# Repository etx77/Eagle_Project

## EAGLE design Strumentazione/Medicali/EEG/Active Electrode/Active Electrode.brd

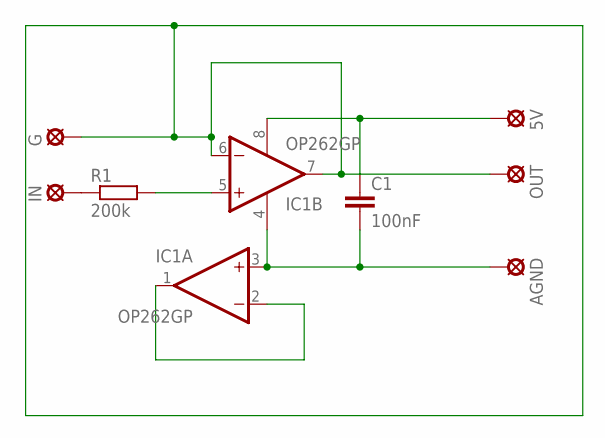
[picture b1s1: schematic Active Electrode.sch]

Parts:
5V: LSP10
AGND: LSP10
C1: 100nF; C025-024X044
G: LSP10
IC1: OP262GP; DIL08
IN: LSP10
OUT: LSP10
R1: 200k; 0204/5

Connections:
unnamed: IC1.1 (OUT), IC1.2 (-IN)
unnamed: AGND.MP, C1.2, IC1.3 (+IN), IC1.4 (V-)
unnamed: IC1.5 (+IN), R1.2
unnamed: IN.MP, R1.1
unnamed: 5V.MP, C1.1, IC1.8 (V+)
unnamed: G.MP, IC1.6 (-IN), IC1.7 (OUT), OUT.MP

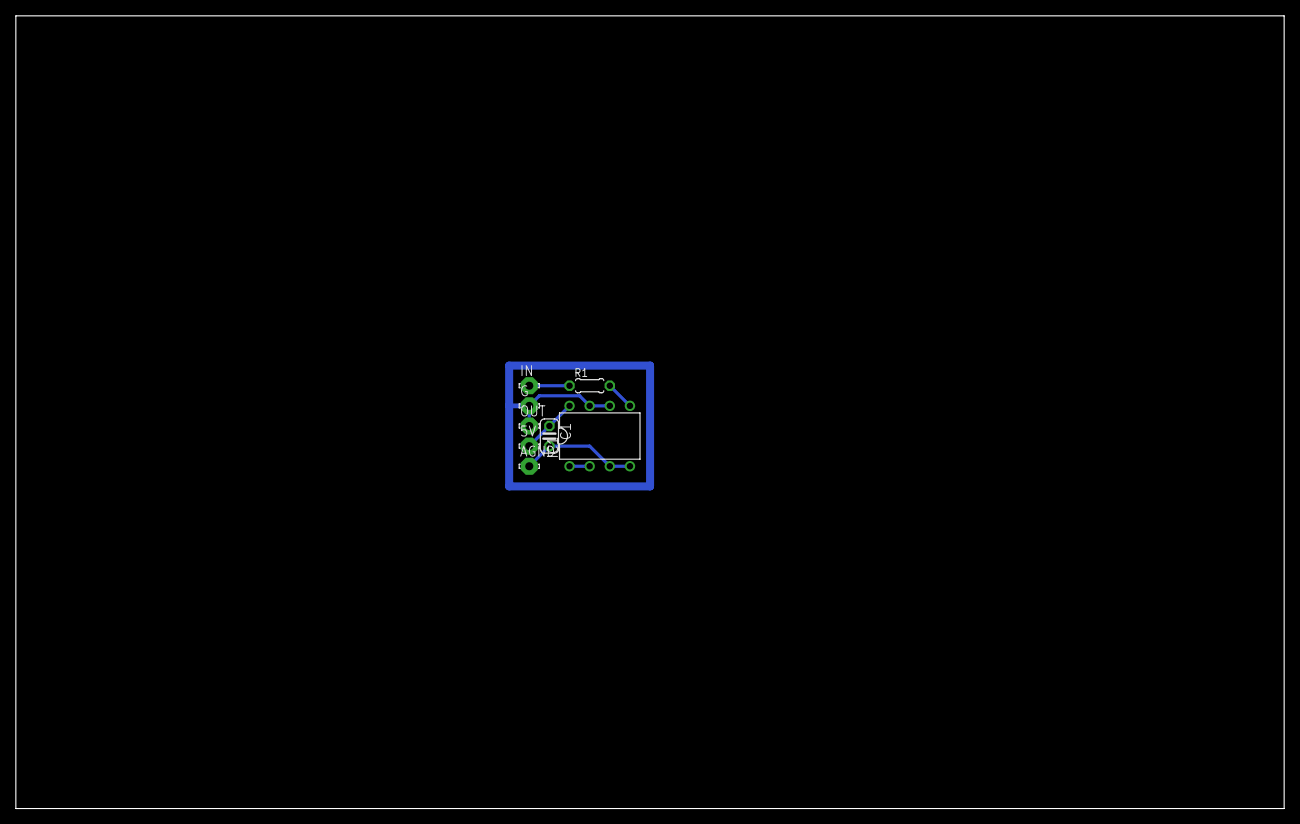
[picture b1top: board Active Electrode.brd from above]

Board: 2 copper layers, 160.0 x 100.0 mm, 8 parts (0 on the bottom side), 6 nets.

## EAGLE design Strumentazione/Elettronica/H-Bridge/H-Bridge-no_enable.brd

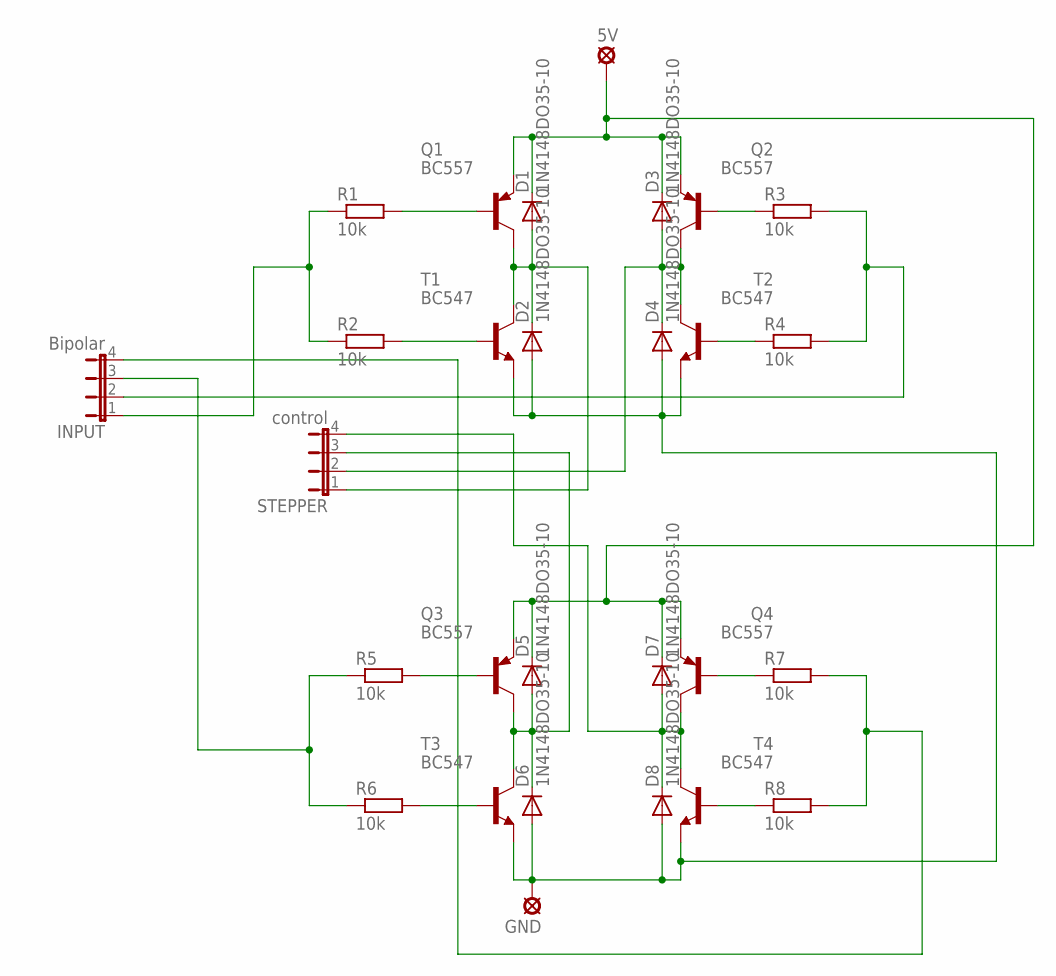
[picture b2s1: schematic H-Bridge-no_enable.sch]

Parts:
5V: LSP10
D1, D2, D3, D4, D5, D6, D7, D8: 1N4148DO35-10; DO35-10
GND: LSP10
INPUT: Bipolar; JP4
Q1, Q2, Q3, Q4: BC557; TO92
R1, R2, R3, R4, R5, R6, R7, R8: 10k; 0204V
STEPPER: control; JP4
T1, T2, T3, T4: BC547; TO92

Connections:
unnamed: INPUT.1, R1.1, R2.1
unnamed: Q1.2 (B), R1.2
unnamed: R2.2, T1.2 (B)
unnamed: D1.A, D2.C, Q1.3 (C), STEPPER.1, T1.3 (C)
unnamed: D3.A, D4.C, Q2.3 (C), STEPPER.2, T2.3 (C)
unnamed: Q2.2 (B), R3.1
unnamed: R4.1, T2.2 (B)
unnamed: INPUT.2, R3.2, R4.2
unnamed: D2.A, D4.A, D6.A, D8.A, GND.MP, T1.1 (E), T2.1 (E), T3.1 (E), T4.1 (E)
unnamed: INPUT.3, R5.1, R6.1
unnamed: Q3.2 (B), R5.2
unnamed: R6.2, T3.2 (B)
unnamed: D5.A, D6.C, Q3.3 (C), STEPPER.3, T3.3 (C)
unnamed: D7.A, D8.C, Q4.3 (C), STEPPER.4, T4.3 (C)
unnamed: Q4.2 (B), R7.1
unnamed: R8.1, T4.2 (B)
unnamed: INPUT.4, R7.2, R8.2
unnamed: 5V.MP, D1.C, D3.C, D5.C, D7.C, Q1.1 (E), Q2.1 (E), Q3.1 (E), Q4.1 (E)

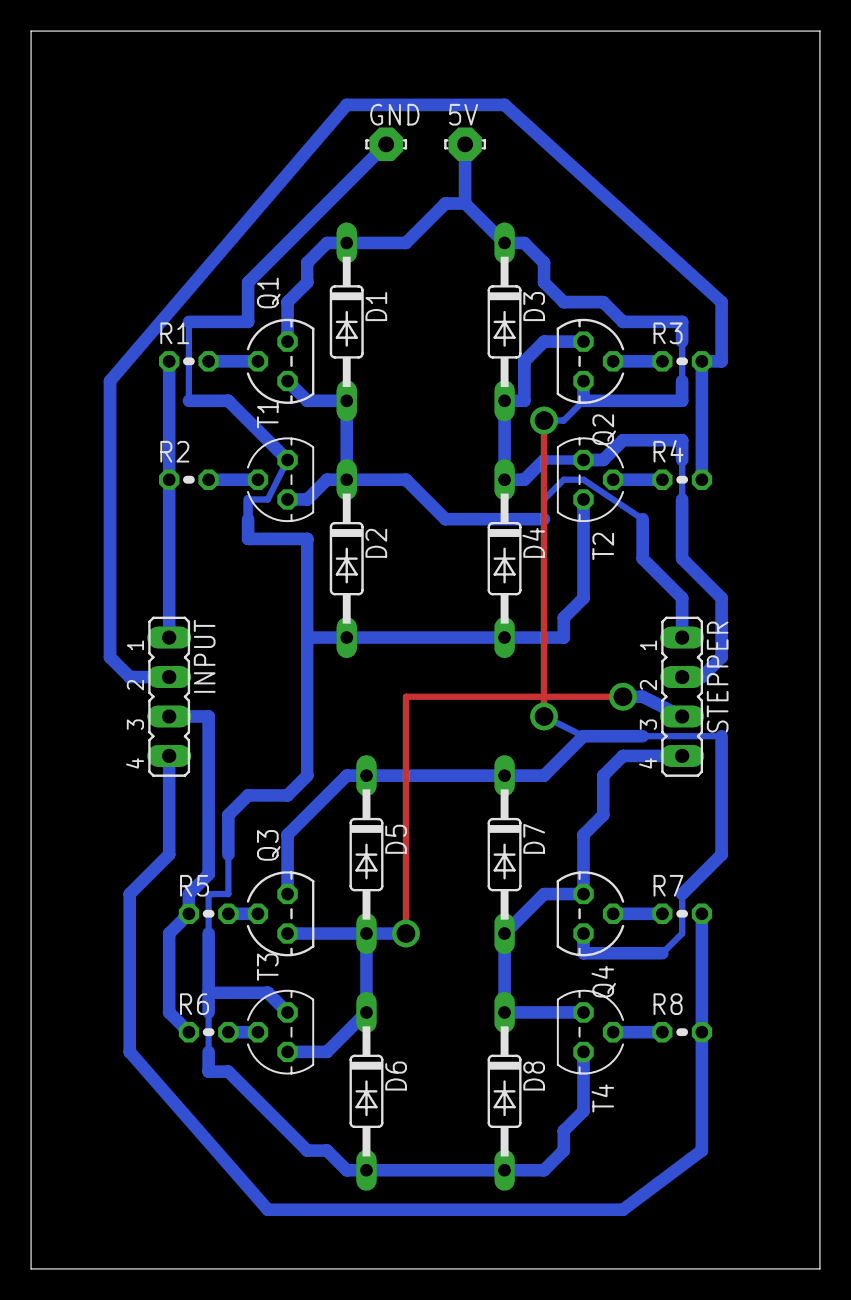
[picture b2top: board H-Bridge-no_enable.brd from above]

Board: 2 copper layers, 50.8 x 79.7 mm, 28 parts (0 on the bottom side), 18 nets.

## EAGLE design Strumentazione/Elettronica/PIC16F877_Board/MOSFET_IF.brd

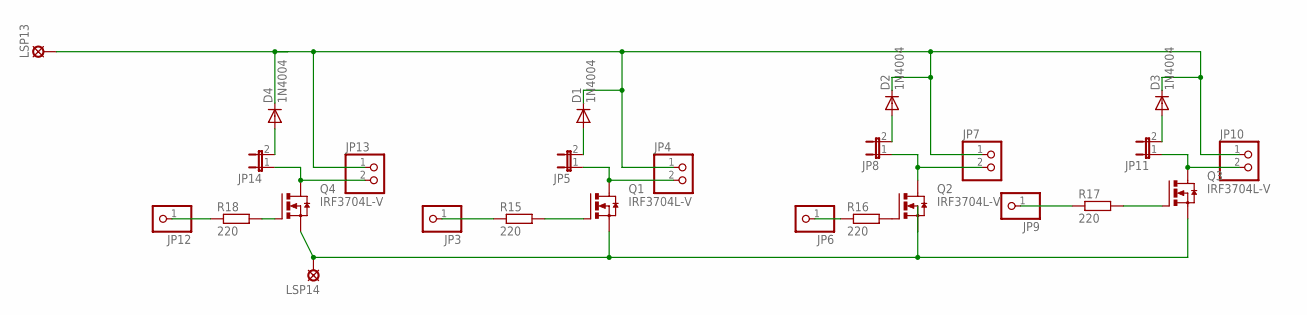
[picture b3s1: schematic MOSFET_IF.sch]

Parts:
D1, D2, D3, D4: 1N4004; DO41-10
JP3, JP6, JP9, JP12: PINHD-1X1; 1X01
JP4, JP7, JP10, JP13: PINHD-1X2; 1X02
JP5, JP8, JP11, JP14: JP1E; JP1
LSP13, LSP14: LSP10
Q1, Q2, Q3, Q4: IRF3704L-V; TO262-V
R15, R16, R17, R18: 220; 0207/10

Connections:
unnamed: Q1.1 (G), R15.2
unnamed: JP3.1, R15.1
unnamed: JP4.2, JP5.1, Q1.2 (D)
unnamed: D1.A, JP5.2
unnamed: Q2.1 (G), R16.2
unnamed: JP6.1, R16.1
unnamed: JP7.2, JP8.1, Q2.2 (D)
unnamed: D2.A, JP8.2
unnamed: Q3.1 (G), R17.2
unnamed: JP9.1, R17.1
unnamed: JP10.2, JP11.1, Q3.2 (D)
unnamed: D3.A, JP11.2
unnamed: Q4.1 (G), R18.2
unnamed: JP12.1, R18.1
unnamed: JP13.2, JP14.1, Q4.2 (D)
unnamed: D4.A, JP14.2
unnamed: D1.C, D2.C, D3.C, D4.C, JP4.1, JP7.1, JP10.1, JP13.1, LSP13.MP
unnamed: LSP14.MP, Q1.3 (S), Q2.3 (S), Q3.3 (S), Q4.3 (S)

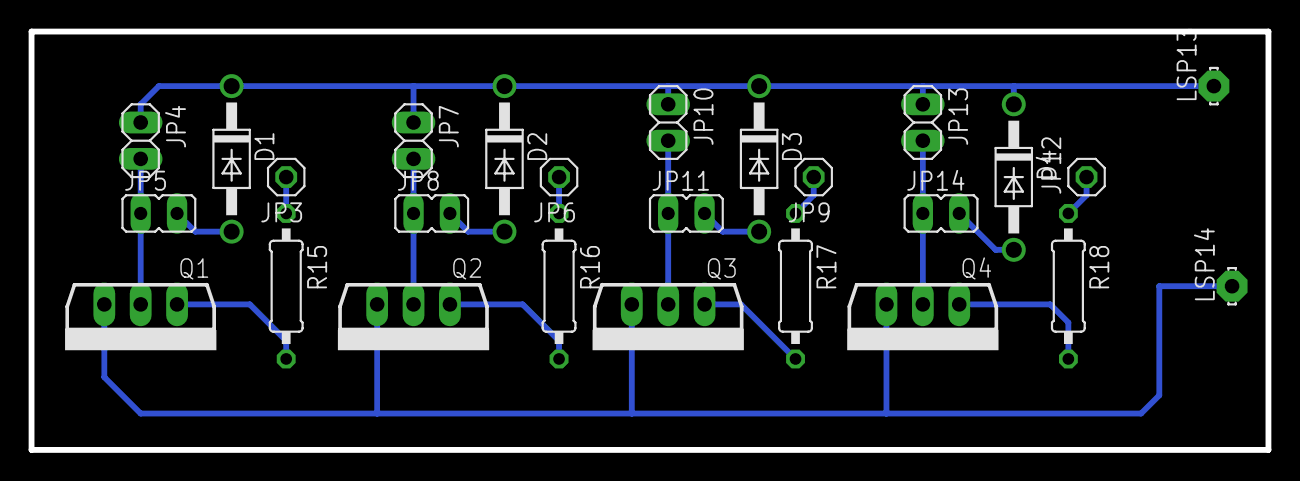
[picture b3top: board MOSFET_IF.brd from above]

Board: 2 copper layers, 86.4 x 29.2 mm, 26 parts (0 on the bottom side), 18 nets.

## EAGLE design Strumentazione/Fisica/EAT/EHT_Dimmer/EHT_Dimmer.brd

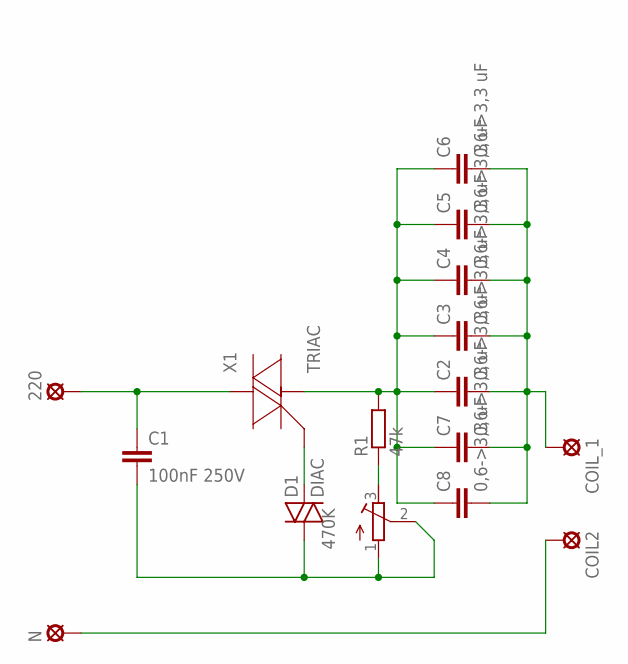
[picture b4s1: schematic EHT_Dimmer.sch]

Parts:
220: LSP10
470K: R-TRIMM3339P; RTRIM3339P
C1: 100nF 250V; C102_152-062X184
C2, C3, C4, C5, C6, C7, C8: 0,6->3,3 uF; C102_152-062X184
COIL2: LSP10
COIL_1: LSP10
D1: DIAC; GT32
N: LSP10
R1: 47k; 0207/10
X1: TRIAC; BR220S

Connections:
unnamed: 220.MP, C1.1, X1.T3 (MT2)
unnamed: C2.1, C3.1, C4.1, C5.1, C6.1, C7.1, C8.1, R1.2, X1.T2 (MT1)
unnamed: 470K.3 (E), R1.1
unnamed: 470K.1 (A), 470K.2 (S), C1.2, D1.1
unnamed: D1.2, X1.T1 (G)
unnamed: C2.2, C3.2, C4.2, C5.2, C6.2, C7.2, C8.2, COIL_1.MP
unnamed: COIL2.MP, N.MP

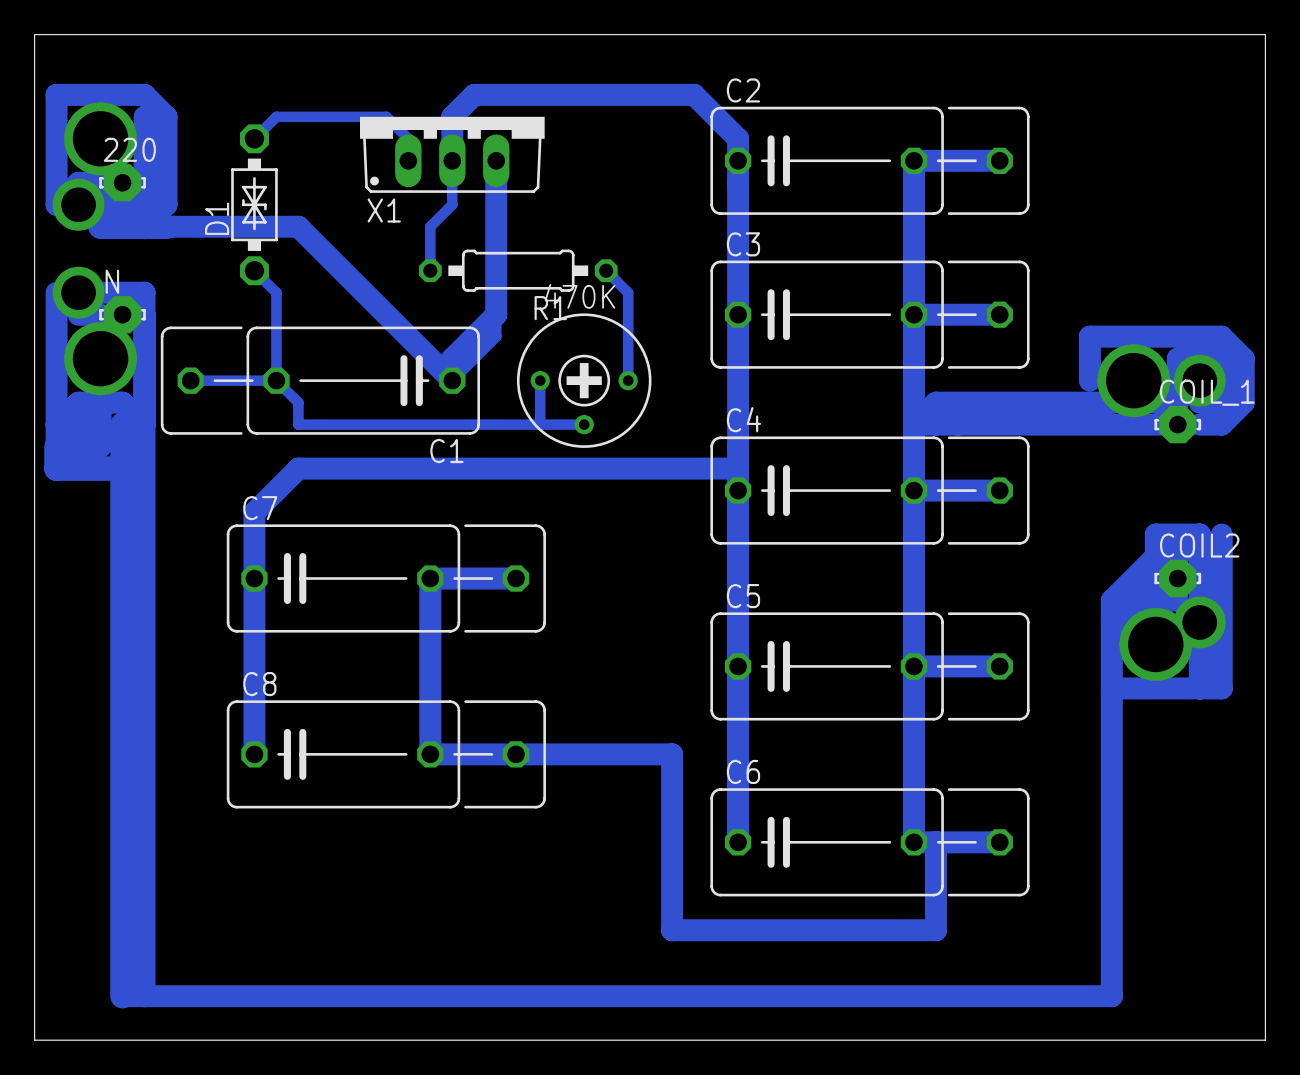
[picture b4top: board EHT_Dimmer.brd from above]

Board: 2 copper layers, 71.1 x 58.1 mm, 16 parts (0 on the bottom side), 7 nets.

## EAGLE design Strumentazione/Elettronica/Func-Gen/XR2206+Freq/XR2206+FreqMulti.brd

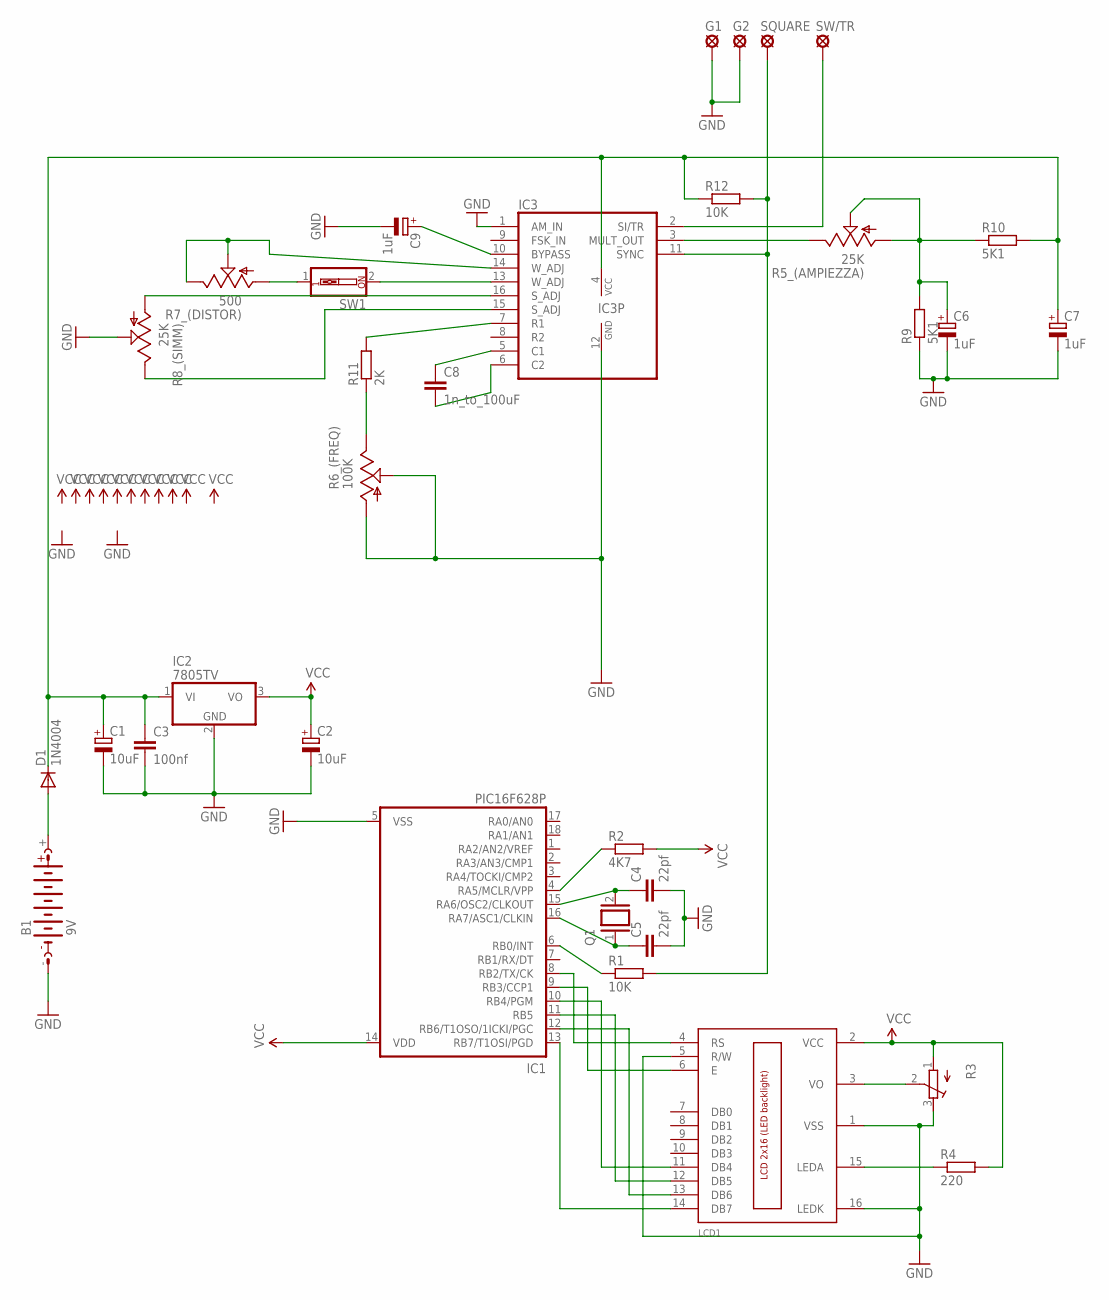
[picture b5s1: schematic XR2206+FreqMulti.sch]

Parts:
B1: 9V; AB9V
C1, C2: 10uF; E2-4
C3: 100nf; C050-025X075
C4, C5: 22pf; C050-025X075
C6, C7, C9: 1uF; E2,5-6E
C8: 1n_to_100uF; C050-030X075
D1: 1N4004; DO41-10
G1, G2: LSP10
IC1: PIC16F628P; DIL18
IC2: 7805TV; TO220V
IC3: XR-2206; DIL16
LCD1: LCD_2X16; HY-1602F
Q1: XTAL/S; QS
R1, R12: 10K; 0207/12
R2: 4K7; 0207/12
R3: R-TRIMM3339P; RTRIM3339P
R4: 220; 0207/12
R5_(AMPIEZZA), R8_(SIMM): 25K; EVUEXXJ
R6_(FREQ): 100K; EVUEXXJ
R7_(DISTOR): 500; EVUEXXJ
R9, R10: 5K1; 0207/12
R11: 2K; 0207/12
SQUARE: LSP10
SW1: SW_DIP-1; EDG-01
SW/TR: LSP10

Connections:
unnamed: LCD1.15 (LEDA), R4.1
unnamed: C4.1, IC1.15 (RA6/OSC2/CLKOUT), Q1.2
unnamed: C5.1, IC1.16 (RA7/ASC1/CLKIN), Q1.1
unnamed: IC1.6 (RB0/INT), R1.1
unnamed: IC1.4 (RA5/MCLR/VPP), R2.1
unnamed: B1.+, D1.A
unnamed: C9.+, IC3.10 (BYPASS)
unnamed: IC1.8 (RB2/TX/CK), LCD1.4 (RS)
unnamed: IC1.9 (RB3/CCP1), LCD1.6 (E)
unnamed: IC3.11 (SYNC), R1.2, R12.2, SQUARE.MP
unnamed: LCD1.3 (VO), R3.2 (S)
unnamed: IC1.10 (RB4/PGM), LCD1.11 (DB4)
unnamed: IC1.11 (RB5), LCD1.12 (DB5)
unnamed: IC1.12 (RB6/T1OSO/1ICKI/PGC), LCD1.13 (DB6)
unnamed: IC1.13 (RB7/T1OSI/PGD), LCD1.14 (DB7)
unnamed: C8.1, IC3.5 (C1)
unnamed: C8.2, IC3.6 (C2)
unnamed: IC3.7 (R1), R11.2
unnamed: R6_(FREQ).3 (E), R11.1
unnamed: IC3.13 (W_ADJ), SW1.2
unnamed: B1.-, C1.-, C2.-, C3.2, C4.2, C5.2, C6.-, C7.-, C9.-, G1.MP, G2.MP, IC1.5 (VSS), IC2.2 (GND), IC3.1 (AM_IN), IC3.12 (GND), LCD1.1 (VSS), LCD1.5 (R/W), LCD1.16 (LEDK), R3.3 (E), R6_(FREQ).1 (A), R6_(FREQ).2 (S), R8_(SIMM).2 (S), R9.1
unnamed: R7_(DISTOR).1 (A), SW1.1
unnamed: IC3.14 (W_ADJ), R7_(DISTOR).2 (S), R7_(DISTOR).3 (E)
unnamed: IC3.16 (S_ADJ), R8_(SIMM).1 (A)
unnamed: IC3.15 (S_ADJ), R8_(SIMM).3 (E)
unnamed: IC3.2 (SI/TR), SW/TR.MP
unnamed: C2.+, IC2.3 (VO), LCD1.2 (VCC), R2.2, R3.1 (A), R4.2
unnamed: C1.+, C3.1, C7.+, D1.C, IC2.1 (VI), IC3.4 (VCC), R10.2, R12.1
unnamed: C6.+, R5_(AMPIEZZA).1 (A), R5_(AMPIEZZA).2 (S), R9.2, R10.1
unnamed: IC3.3 (MULT_OUT), R5_(AMPIEZZA).3 (E)
VCC: IC1.14 (VDD)

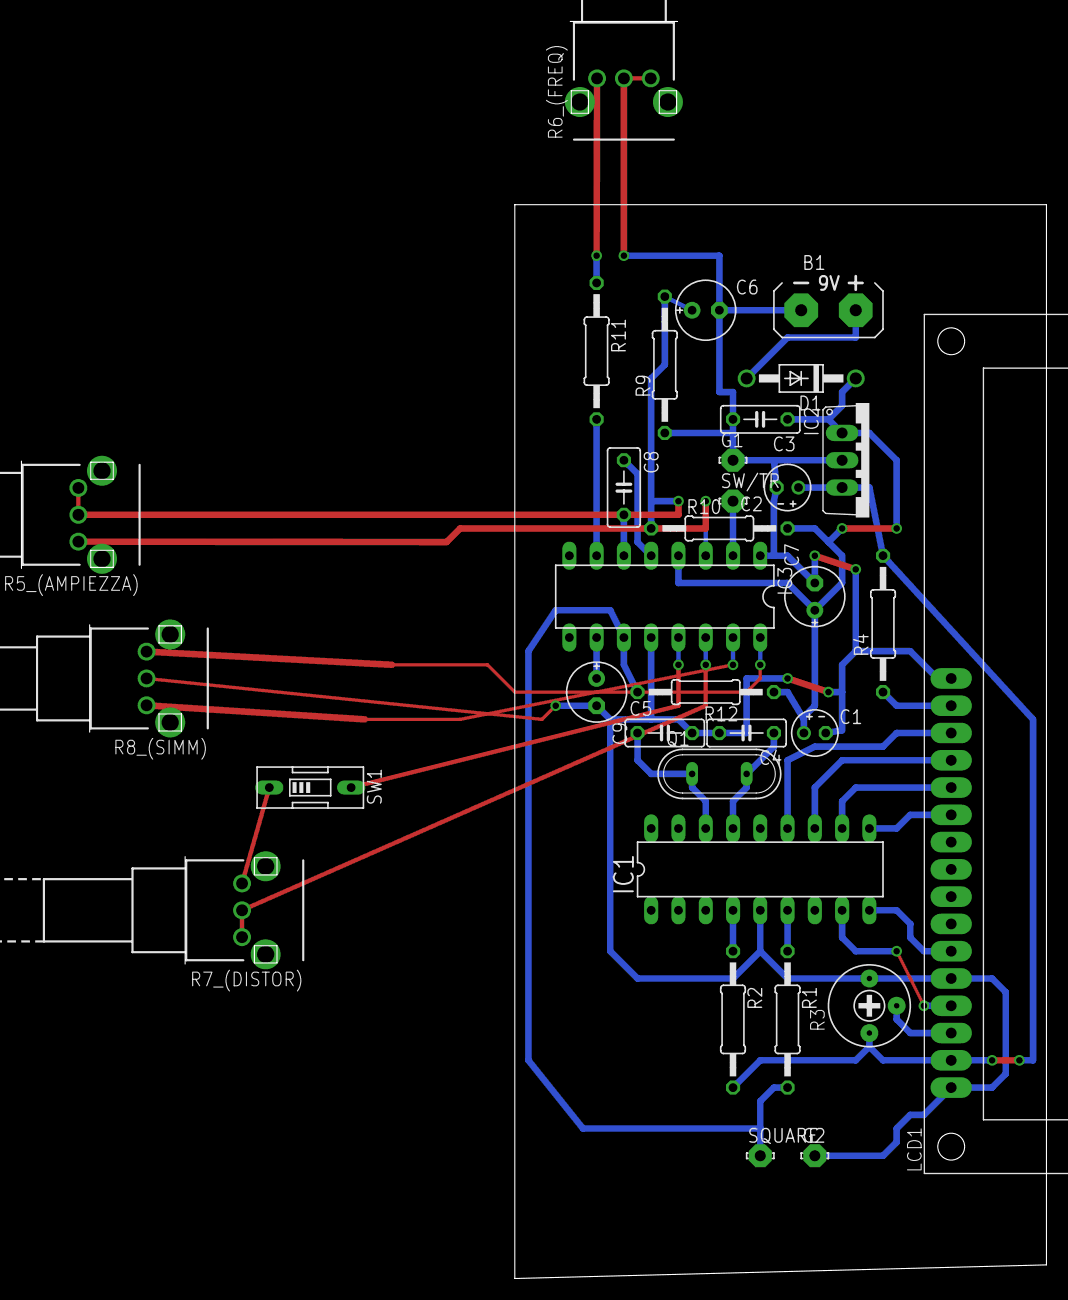
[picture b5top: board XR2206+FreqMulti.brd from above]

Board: 2 copper layers, 49.5 x 100.0 mm, 33 parts (0 on the bottom side), 30 nets.

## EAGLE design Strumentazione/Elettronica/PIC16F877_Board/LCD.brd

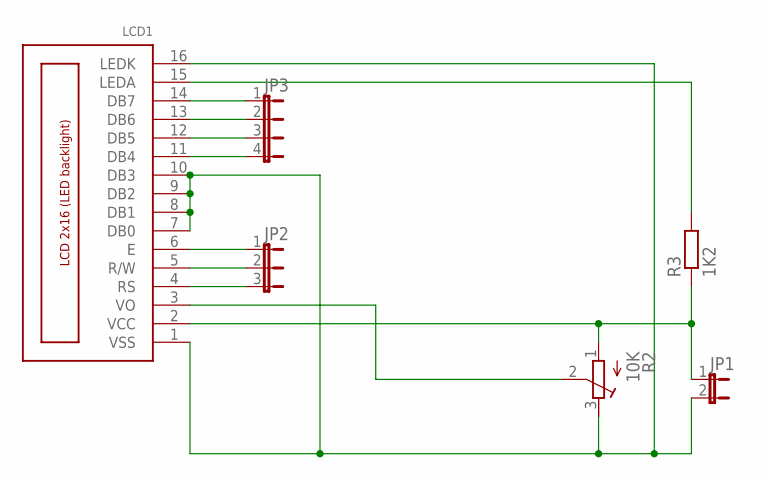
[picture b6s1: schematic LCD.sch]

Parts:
JP1: JP1E; JP1
JP2: JP2E; JP2
JP3: JP4E; JP4
LCD1: LCD_2X16_SIL; HY-1602F
R2: 10K; RTRIM3339P
R3: 1K2; 0207/10

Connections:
unnamed: JP1.1, LCD1.2 (VCC), R2.1 (A), R3.1
unnamed: LCD1.15 (LEDA), R3.2
unnamed: LCD1.3 (VO), R2.2 (S)
unnamed: JP1.2, LCD1.1 (VSS), LCD1.7 (DB0), LCD1.8 (DB1), LCD1.9 (DB2), LCD1.10 (DB3), LCD1.16 (LEDK), R2.3 (E)
unnamed: JP3.1, LCD1.14 (DB7)
unnamed: JP3.2, LCD1.13 (DB6)
unnamed: JP3.3, LCD1.12 (DB5)
unnamed: JP3.4, LCD1.11 (DB4)
unnamed: JP2.1, LCD1.6 (E)
unnamed: JP2.2, LCD1.5 (R/W)
unnamed: JP2.3, LCD1.4 (RS)

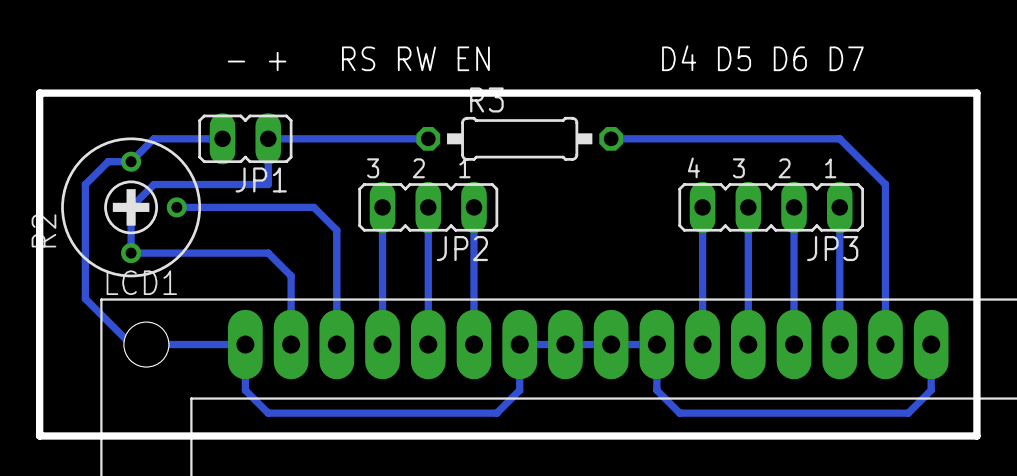
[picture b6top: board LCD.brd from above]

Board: 2 copper layers, 52.1 x 19.1 mm, 6 parts (0 on the bottom side), 11 nets.

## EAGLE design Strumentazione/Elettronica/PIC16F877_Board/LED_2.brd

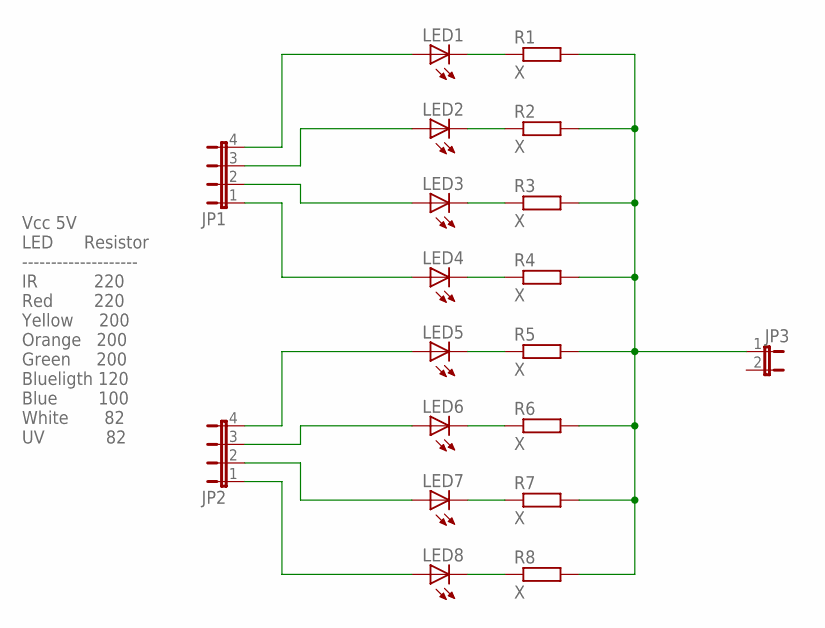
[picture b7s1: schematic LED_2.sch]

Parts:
JP1, JP2: JP4E; JP4
JP3: JP1E; JP1
LED1, LED2, LED3, LED4, LED5, LED6, LED7, LED8: LED5MM
R1, R2, R3, R4, R5, R6, R7, R8: X; 0411V

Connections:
unnamed: LED2.K (C), R2.1
unnamed: LED3.K (C), R3.1
unnamed: LED4.K (C), R4.1
unnamed: LED5.K (C), R5.1
unnamed: LED6.K (C), R6.1
unnamed: LED7.K (C), R7.1
unnamed: LED8.K (C), R8.1
unnamed: LED1.K (C), R1.1
unnamed: JP1.4, LED1.A
unnamed: JP1.3, LED2.A
unnamed: JP1.2, LED3.A
unnamed: JP1.1, LED4.A
unnamed: JP2.4, LED5.A
unnamed: JP2.3, LED6.A
unnamed: JP2.2, LED7.A
unnamed: JP2.1, LED8.A
unnamed: JP3.1, R1.2, R2.2, R3.2, R4.2, R5.2, R6.2, R7.2, R8.2

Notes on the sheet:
Vcc 5V LED Resistor -------------------- IR 220 Red 220 Yellow 200 Orange 200 Green 200 Blueligth 120 Blue 100 White 82 UV 82

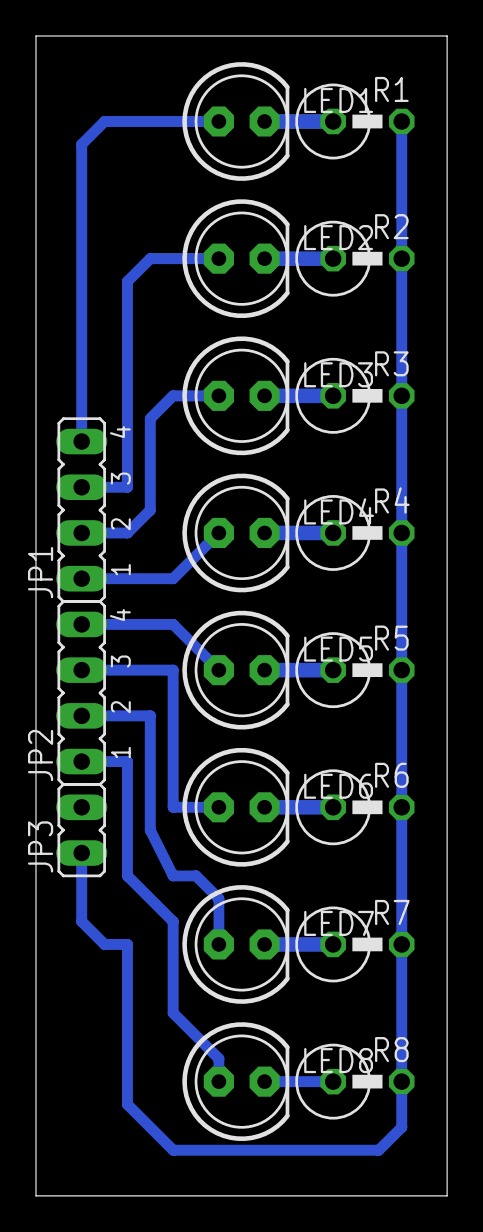
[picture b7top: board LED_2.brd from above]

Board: 2 copper layers, 22.8 x 64.4 mm, 19 parts (0 on the bottom side), 17 nets.

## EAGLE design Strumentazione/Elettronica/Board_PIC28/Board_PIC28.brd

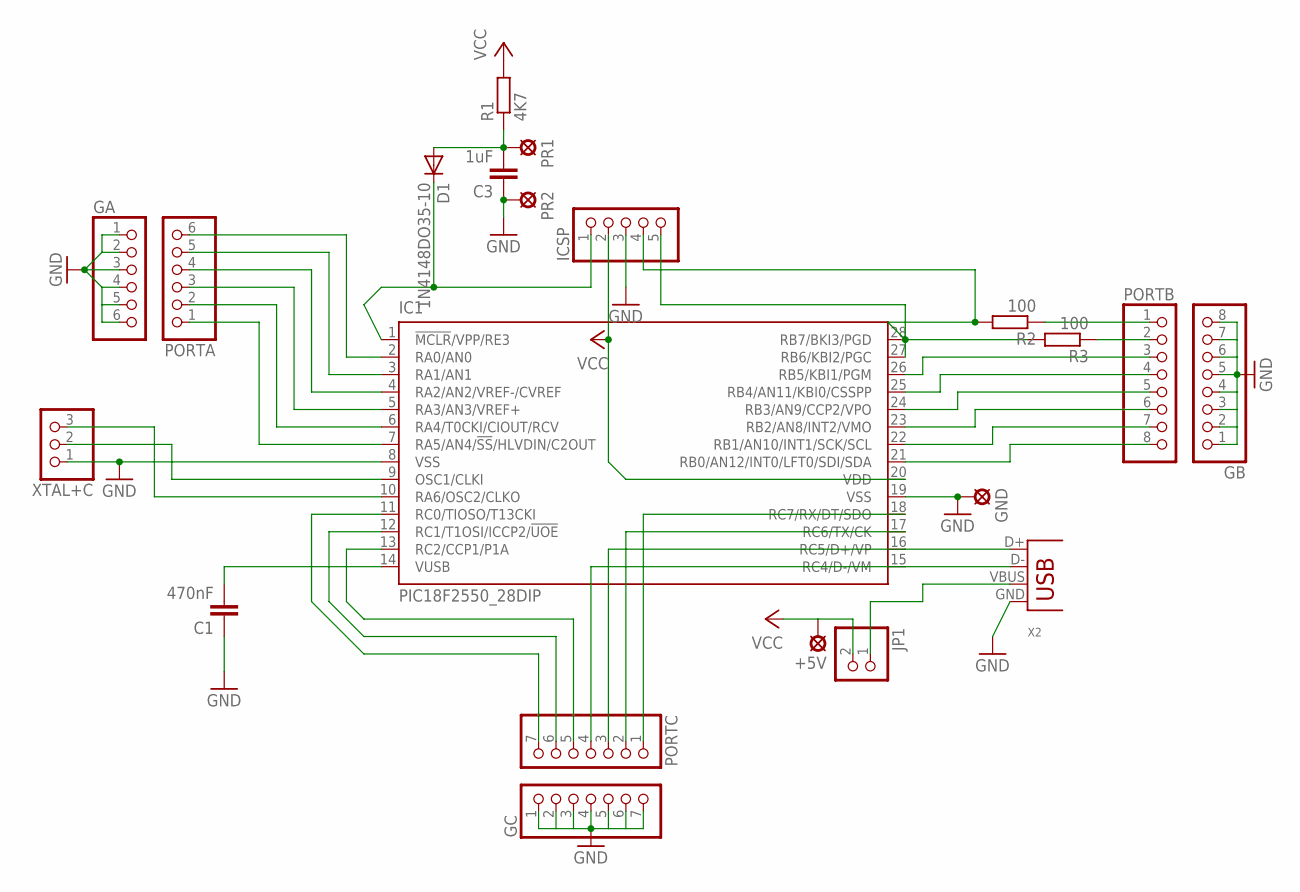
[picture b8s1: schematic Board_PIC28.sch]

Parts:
+5V: LSP10
C1: 470nF; C5B3.5
C3: 1uF; C5B3.5
D1: 1N4148DO35-10; DO35-10
GA: PINHD-1X6; 1X06
GB: PINHD-1X8; 1X08
GC: PINHD-1X7; 1X07
GND: LSP10
IC1: PIC18F2550_28DIP; DIL28-3
ICSP: PINHD-1X5; 1X05
JP1: PINHD-1X2; 1X02
PORTA: PINHD-1X6; 1X06
PORTB: PINHD-1X8; 1X08
PORTC: PINHD-1X7; 1X07
PR1, PR2: LSP10
R1: 4K7; 0204/7
R2, R3: 100; 0204/7
X2: USB-B-H
XTAL+C: PINHD-1X3; 1X03

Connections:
GND: C1.1, C3.1, GA.1, GA.2, GA.3, GA.4, GA.5, GA.6, GB.1, GB.2, GB.3, GB.4, GB.5, GB.6, GB.7, GB.8, GC.1, GC.2, GC.3, GC.4, GC.5, GC.6, GC.7, GND.MP, IC1.8 (VSS), IC1.19 (VSS), ICSP.3, PR2.MP, X2.GND, XTAL+C.1
unnamed: C3.2, D1.A, PR1.MP, R1.1
unnamed: IC1.2 (RA0/AN0), PORTA.6
unnamed: IC1.28 (RB7/BKI3/PGD), ICSP.4, R2.2
unnamed: IC1.27 (RB6/KBI2/PGC), ICSP.5, R3.2
unnamed: IC1.26 (RB5/KBI1/PGM), PORTB.3
unnamed: IC1.25 (RB4/AN11/KBI0/CSSPP), PORTB.4
unnamed: IC1.24 (RB3/AN9/CCP2/VPO), PORTB.5
unnamed: IC1.23 (RB2/AN8/INT2/VMO), PORTB.6
unnamed: IC1.22 (RB1/AN10/INT1/SCK/SCL), PORTB.7
unnamed: IC1.21 (RB0/AN12/INT0/LFT0/SDI/SDA), PORTB.8
unnamed: IC1.16 (RC5/D+/VP), PORTC.3, X2.D+
unnamed: IC1.15 (RC4/D-/VM), PORTC.4, X2.D-
unnamed: IC1.13 (RC2/CCP1/P1A), PORTC.5
unnamed: IC1.12 (RC1/T1OSI/ICCP2/!UOE), PORTC.6
unnamed: IC1.11 (RC0/TIOSO/T13CKI), PORTC.7
unnamed: IC1.10 (RA6/OSC2/CLKO), XTAL+C.3
unnamed: IC1.9 (OSC1/CLKI), XTAL+C.2
unnamed: D1.C, IC1.1 (!MCLR!/VPP/RE3), ICSP.1
unnamed: IC1.3 (RA1/AN1), PORTA.5
unnamed: IC1.4 (RA2/AN2/VREF-/CVREF), PORTA.4
unnamed: IC1.5 (RA3/AN3/VREF+), PORTA.3
unnamed: IC1.6 (RA4/T0CKI/CIOUT/RCV), PORTA.2
unnamed: IC1.7 (RA5/AN4/!SS!/HLVDIN/C2OUT), PORTA.1
unnamed: PORTB.1, R2.1
unnamed: PORTB.2, R3.1
unnamed: C1.2, IC1.14 (VUSB)
unnamed: JP1.1, X2.VBUS
unnamed: IC1.17 (RC6/TX/CK), PORTC.2
unnamed: IC1.18 (RC7/RX/DT/SDO), PORTC.1
VCC: +5V.MP, IC1.20 (VDD), ICSP.2, JP1.2, R1.2

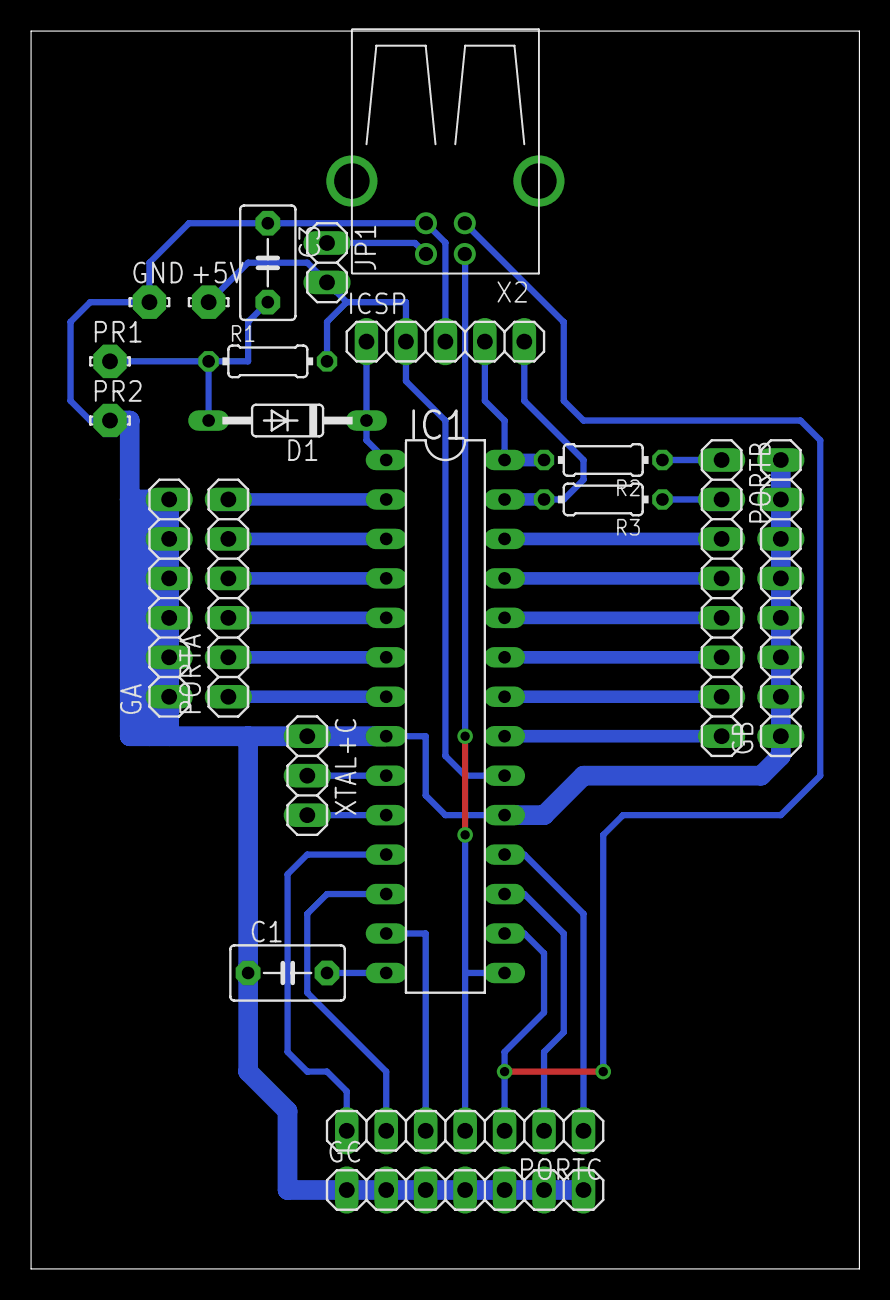
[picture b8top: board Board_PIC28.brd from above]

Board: 2 copper layers, 53.3 x 79.7 mm, 21 parts (0 on the bottom side), 31 nets.

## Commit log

2018-04-26 first

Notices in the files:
parts and their libraries:
SparkFun-Aesthetics: Licensing: Creative Commons ShareAlike 4.0 International - https://creativecommons.org/licenses/by-sa/4.0
